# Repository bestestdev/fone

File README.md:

# fone

A modern take on the classic Nokia cell phone experience, built with a Raspberry Pi Pico 2 running MicroPython. This project combines the simplicity and reliability of old-school Nokia phones with quality-of-life improvements for modern usability.

## Overview

**fone** is a DIY cellular phone that captures the essence of classic Nokia devices while incorporating modern components and conveniences. The device features a minimalist design focused on essential communication functions: calls, SMS, and basic navigation, all powered by MicroPython for easy customization and development.

## Hardware Components

### Core Processing
- **Raspberry Pi Pico 2** - Main microcontroller running MicroPython
- **W25Q128 SPI Flash** - 16MB flash storage for contacts, messages, and system data

### Cellular Communication
- **SIM7600G Module** - 4G/LTE cellular connectivity with GPS
- Connected via UART (TX/RX) to Pico 2

### Power Management
- **3700mAh Lithium Battery** - Long-lasting power source
- **TP4056 Charging Module** - Safe battery charging via USB-C
- **MT3608 Boost Converter** - Boost LiPo battery to 5v for use by the SIM module and Pico

### Audio System
- **MAX98357A I2S Amplifier** - Digital audio amplification
- **1W 8Ω Speaker** - Clear audio output for calls and notifications
- **GY-MAX4466 Electret Microphone** - Voice input with AGC
- **ADS1115 ADC** - High-resolution analog-to-digital conversion for microphone

### Display & Input
- **2.42" OLED Display (SSD1309)** - monochrome, 128x64 resolution, SPI interface, low power consumption
- **ANO Directional Navigation and Scroll Wheel Rotary Encoder** - Navigation, selection, scroll, and menu control
- **3V Coin Vibration Motor** - Haptic feedback and notifications

## Features

### Core Functionality
- **Voice Calls** - Make and receive phone calls with clear audio
- **SMS Messaging** - Send and receive text messages
- **Contact Management** - Store and organize phone contacts
- **Call History** - Track incoming, outgoing, and missed calls

### Enhanced User Experience
- **Improved Text Input** - Modern T9-style predictive text with encoder navigation
- **Menu Navigation** - Intuitive interface designed for encoder and directional button control
- **Scroll Wheel Support** - Rotary encoder provides smooth scrolling through lists and menus
- **Low Power Operation** - E-paper display and efficient power management
- **Haptic Feedback** - Vibration for notifications and user interactions

### Additional Features
- **GPS Location (Stretch Goal)** - Built-in positioning via SIM7600G
- **Battery Monitoring** - Real-time battery level and charging status
- **Silent/Vibrate Modes** - Customizable notification preferences
- **Basic Games** - Classic Nokia-style entertainment (Snake, etc.)

## Technical Specifications

### Connectivity
- **Cellular**: 4G LTE via SIM7600G
- **GPS (Stretch Goal)**: Built-in GNSS receiver
- **Storage**: 16MB SPI flash memory (W25Q128)

### Power
- **Battery Life**: All-day usage with 3700mAh capacity
- **Charging**: USB charging via TP4056 module
- **Standby**: Ultra-low power consumption with e-paper display

### Interface
- **Display**: 2.42" monochrome OLED (128x64px)
- **Input**: ANO rotary encoder with directional navigation buttons
- **Audio**: Full-duplex voice communication
- **Feedback**: Vibration motor for alerts

## Software Architecture

- **Platform**: MicroPython on Raspberry Pi Pico 2
- **Modular Design**: Separate modules for cellular, audio, display, and input handling
- **Event-Driven**: Efficient power management through interrupt-based operation
- **Extensible**: Easy to add new features and customize behavior

## Wiring Guide

### SIM7600G to Raspberry Pi Pico 2

The SIM7600G module connects via UART and requires the following connections:

| SIM7600G Pin | Description | Connection | Notes |
|--------------|-------------|------------|-------|
| **V** | VCC | **5V from MT3608** | Requires stable 5V (up to 2A) |
| **G** | Ground | **Battery -** | Battery ground |
| **G** | Ground | **Pico GND** (Pin 38) | Shared ground with Pico |
| **T** | TX (Module transmit) | **GP1** (Pin 2) | UART0 RX |
| **R** | RX (Module receive) | **GP0** (Pin 1) | UART0 TX |
| **K** | Power Key | **GP2** (Pin 4) | GPIO for power control |
| **S** | Status | **GP3** (Pin 5) | GPIO for status monitoring |

#### Key Points:
- **Power**: SIM7600G requires 5V via MT3608 boost converter for proper RF operation
- **Current Draw**: Module can draw up to 2A during transmission bursts
- **UART**: Cross-connect TX/RX (module TX → Pico RX, module RX → Pico TX)
- **Power Key**: Pull HIGH briefly to turn module on/off
- **Status**: Monitor this pin to check if module is powered and ready
- **Dual Ground**: Connect both ground pins for stable operation

### ANO Directional Navigation and Scroll Wheel Rotary Encoder

The primary input is an ANO directional navigation and scroll wheel rotary encoder, providing directional control, rotary scroll input, and a center-press button.

| Encoder Pin | Description | Connection | Notes |
|-------------|-------------|------------|-------|
| **ENCA** | Encoder A Pin | **GP17** (Pin 22) | Rotary encoder quadrature A |
| **ENCB** | Encoder B Pin | **GP22** (Pin 29) | Rotary encoder quadrature B |
| **SW1** | Center Button | **GP6** (Pin 9) | Digital input |
| **SW2** | Down Button | **GP5** (Pin 7) | Digital input |
| **SW3** | Right Button | **GP4** (Pin 6) | Digital input |
| **SW4** | Up Button | **GP19** (Pin 25) | Digital input |
| **SW5** | Left Button | **GP18** (Pin 24) | Digital input |
| **COM** | Common | **GND** (Pin 38) | Common ground for all switches |

#### Key Points:
- **Rotary Encoder**: ENCA/ENCB provide quadrature signals for scroll wheel functionality
- **Digital Buttons**: All switch pins (SW1-SW5) are simple digital inputs
- **Wiring**: Connect the COM pin to GND and configure each GPIO pin as an input with an internal pull-up resistor
- **Active Low**: Button presses and encoder transitions pull pins to ground (LOW)
- **Quadrature Decoding**: Software tracks encoder A/B state changes to determine rotation direction and steps

### Dual Analog Joysticks via ADS1115 ADC

> **Note:** This component has been deprecated and replaced by the ANO Directional Navigation and Scroll Wheel Rotary Encoder.

The phone uses two analog joysticks for navigation and input, connected through an ADS1115 16-bit ADC for full 4-channel analog precision.

**ADS1115 ADC Module:**

| ADS1115 Pin | Description | Connection | Notes |
|-------------|-------------|------------|-------|
| **VDD** | Power | **5V** (Pin 40 - VBUS) | Module power supply |
| **GND** | Ground | **GND** (Pin 38) | Common ground |
| **SCL** | I2C Clock | **GP21** (Pin 27) | I2C0 SCL |
| **SDA** | I2C Data | **GP20** (Pin 26) | I2C0 SDA |
| **ADDR** | Address | **GND** | Sets I2C address to 0x48 |

**Left Joystick (mounted upside down):**

| Joystick Pin | Description | Connection | Notes |
|--------------|-------------|------------|-------|
| **VCC** | Power | **5V** (Pin 40 - VBUS) | Joystick power supply |
| **GND** | Ground | **GND** (Pin 38) | Common ground |
| **VRX** | X-axis analog | **ADS1115 AIN0** | Left joystick X |
| **VRY** | Y-axis analog | **ADS1115 AIN1** | Left joystick Y (inverted) |
| **SW** | Switch button | **GP19** (Pin 25) | Digital input with pull-up |

**Right Joystick:**

| Joystick Pin | Description | Connection | Notes |
|--------------|-------------|------------|-------|
| **VCC** | Power | **5V** (Pin 40 - VBUS) | Joystick power supply |
| **GND** | Ground | **GND** (Pin 38) | Common ground |
| **VRX** | X-axis analog | **ADS1115 AIN2** | Right joystick X |
| **VRY** | Y-axis analog | **ADS1115 AIN3** | Right joystick Y |
| **SW** | Switch button | **GP18** (Pin 24) | Digital input with pull-up |

#### Key Points:
- **Full Analog Control**: ADS1115 provides 4 channels of 16-bit ADC precision
- **I2C Address**: 0x48 (ADDR pin to GND), can be changed for multiple modules
- **Left Joystick**: Mounted upside down, so Y-axis values are inverted in software
- **ADC Resolution**: 16-bit (±32767) with ±4.096V input range matches 5V joysticks
- **Switches**: Active low with internal pull-up resistors on Pico pins (3.3V logic)
- **Update Rate**: ~128 SPS (samples per second) for smooth control

### 3V Vibration Motor

The vibration motor provides haptic feedback for notifications and user interactions.

#### Option 1: Direct GPIO Control (Recommended to try first)

**For Low Current Motors (< 40mA):**

| Motor Pin | Description | Connection | Notes |
|-----------|-------------|------------|-------|
| **+** | Positive | **GP16** (Pin 21) | Direct PWM control |
| **-** | Negative | **GND** (Pin 38) | Direct ground connection |

#### Option 2: Transistor-Protected Control

**For Higher Current Motors (> 40mA) or if direct control fails:**

| Motor Pin | Description | Connection | Notes |
|-----------|-------------|------------|-------|
| **+** | Positive | **GP16** (Pin 21) via NPN Transistor | PWM-controlled output |
| **-** | Negative | **GND** (Pin 38) | Direct ground connection |

**Transistor Circuit (NPN - 2N2222 or similar):**

| Transistor Pin | Description | Connection | Notes |
|----------------|-------------|------------|-------|
| **Base** | Control | **GP16** (Pin 21) via 1kΩ resistor | PWM signal from Pico |
| **Collector** | High side | **Motor +** | Connects to motor positive |
| **Emitter** | Ground | **GND** (Pin 38) | Common ground |

#### Key Points:
- **Motor Specs**: 3V, 12000 RPM, small coin-type vibration motor
- **Current Draw**: Small motors (17-35mA) can connect directly, larger motors (60-105mA) need transistor
- **Pico GPIO Limits**: ~16mA safe, ~50mA maximum per pin
- **Try Direct First**: Start with Option 1 - if motor doesn't work well or Pico gets warm, use Option 2
- **Flyback Diode**: Optional 1N4001 diode across motor (cathode to +, anode to -) for back-EMF protection
- **Control**: PWM control via GP16 allows variable vibration intensity
- **Frequency**: Typical vibration patterns: short bursts (100-300ms) for notifications

### 2.42" OLED Display (SSD1309)

The 2.42" monochrome OLED display provides the main user interface with a 128x64 resolution using SPI communication.

**Display Module Connections:**

| Display Pin | Description | Connection | Notes |
|-------------|-------------|------------|-------|
| **VCC** | Power | **3V3** (Pin 36) | 3.3V power supply |
| **GND** | Ground | **GND** (Pin 38) | Common ground |
| **CLK** | SPI Clock | **GP10** (Pin 14) | SPI1 SCK |
| **DIN** | SPI Data In | **GP11** (Pin 15) | SPI1 MOSI (TX) |
| **CS** | Chip Select | **GP9** (Pin 12) | SPI chip select (active low) |
| **DC** | Data/Command | **GP12** (Pin 16) | Command mode control |
| **RST** | Reset | **GP13** (Pin 17) | Hardware reset (active low) |

#### Key Points:
- **SPI Interface**: Uses SPI1 on Pico 2 for communication
- **Monochrome Display**: Black and white output with high contrast
- **Resolution**: 128x64 pixels provides clear text and simple graphics
- **Fast Updates**: ~10ms refresh time for full screen updates
- **Low Power**: Efficient power consumption (perfect for phone standby)
- **Rotation Support**: Software rotation for portrait or landscape orientation
- **Viewing Angle**: Wide viewing angle (>160°) for clear visibility
- **Compact Size**: 2.42" diagonal with minimal bezel

### W25Q128 SPI Flash Memory Module

The W25Q128 provides 16MB (128Mbit) of non-volatile storage for contacts, messages, and system data, connected via SPI interface. This flash memory offers faster access times and lower power consumption compared to SD cards.

**W25Q128 Module Connections:**

| W25Q128 Pin | Description | Connection | Notes |
|-------------|-------------|------------|-------|
| **VCC** | Power | **3V3** (Pin 36) | 3.3V power supply |
| **GND** | Ground | **GND** (Pin 38) | Common ground |
| **DC** | SPI Data Out (MISO) | **GP8** (Pin 11) | SPI1 MISO (RX) |
| **D1** | SPI Data In (MOSI) | **GP11** (Pin 15) | SPI1 MOSI (TX) - **Shared with display** |
| **SLK** | SPI Clock | **GP10** (Pin 14) | SPI1 SCK - **Shared with display** |
| **CS** | Chip Select | **GP7** (Pin 10) | SPI chip select (active low) |

#### Key Points:
- **Shared SPI Bus**: Uses SPI1 shared with the e-paper display (SLK, D0 pins)
- **Separate MISO**: Flash memory has its own MISO line (D1/GP8) since display is write-only
- **Unique CS**: Each device has its own chip select (Flash: GP7, Display: GP9)
- **Power**: 3.3V operation, low power consumption (4mA active, <1µA standby)
- **Storage**: 16MB of flash memory with 100,000+ erase/program cycles
- **Performance**: Up to 104MHz SPI clock, much faster than SD card access
- **File System**: Can use LittleFS or FAT filesystem via MicroPython's VFS

### MAX98357A I2S Amplifier and Speaker

The MAX98357A is a digital I2S audio amplifier used to drive the speaker for calls, notifications, and other audio feedback.

**MAX98357A Module Connections:**

| MAX98357A Pin | Description | Connection | Notes |
|---------------|-------------|------------|-------|
| **Vin** | Power In | **5V** (Pin 40 - VBUS) | 3-5.5V input range |
| **GND** | Ground | **GND** (Pin 38) | Common ground |
| **DIN** | Data In | **GP20** (Pin 26) | I2S Serial Data |
| **BCLK** | Bit Clock | **GP14** (Pin 19) | I2S Bit Clock |
| **LRC** | Left-Right Clock | **GP15** (Pin 20) | I2S Word Select |
| **SD** | Shutdown | **GP21** (Pin 27) | Active-low shutdown control |
| **GAIN** | Gain Select | *(unconnected)* | Default 9dB gain. Connect to GND for 3dB, VCC for 15dB. |

**Speaker Connection:**

| Component | Connection |
|-----------|------------|
| **Speaker +** | **MAX98357A Left/Right +** |
| **Speaker -** | **MAX98357A Left/Right -** |

#### Key Points:
- **I2S Audio**: Digital audio provides clear, noise-free sound.
- **Power**: Connected to 5V for maximum speaker volume.
- **Shutdown Pin**: GP21 controls the amplifier's shutdown mode to conserve power.
- **Mono Output**: Although the module has L/R outputs, it's a mono amplifier. Connect speaker to either pair.
- **Gain Control**: The `GAIN` pin can be used to adjust the amplification level if needed. Default (unconnected) is 9dB.

### GY-MAX4466 Electret Microphone

The GY-MAX4466 microphone module with automatic gain control (AGC) is used for voice input. It's connected directly to one of the Pico's ADC pins.

**Microphone Module Connections:**

| Microphone Pin | Description | Connection | Notes |
|----------------|-------------|------------|-------|
| **VCC** | Power | **3V3** (Pin 36) | 2.4-5.5V input range |
| **GND** | Ground | **GND** (Pin 38) | Common ground |
| **OUT** | Analog Out | **GP28** (Pin 34) | Connects to ADC2 |

#### Key Points:
- **Direct ADC Connection**: Simplifies wiring and reduces component count.
- **Analog Pin**: Uses `GP28`, one of the Pico's three dedicated ADC pins.
- **Power**: Runs on 3.3V power provided by the Pico.
- **AGC**: The MAX4466's automatic gain control adjusts for varying sound levels.

### Battery Level Monitoring

To monitor the battery level, a voltage divider is used to scale the battery's voltage (3.0V-4.2V) down to a range the Pico's ADC can safely read (0-3.3V). The reading is taken on the now-available ADC pin.

**Voltage Divider Circuit:**

| Component | Connection | Notes |
|-----------|----------------------------------|---------------------------------------|
| **Battery +** | Resistor 1 (R1) - e.g., 100kΩ | Connects to the positive battery terminal |
| **R1 + R2** | **GP26** (Pin 31) & Resistor 2 (R2) | Center point connects to Pico's ADC pin |
| **R2** | **GND** (Pin 38) | Connects to ground |

*A 1:1 ratio (e.g., two 100kΩ resistors) is simple and effective.*

**Pin Connection:**

| Description | Connection | Notes |
|-------------------|------------|----------------------------|
| **Voltage Sense** | **GP26** (Pin 31) | ADC capable pin (ADC0) |

#### Key Points:
- **Voltage Divider**: Essential to prevent damage to the Pico's ADC.
- **Resistor Choice**: Using identical resistors (e.g., 100kΩ) creates a simple 1:2 divider. The actual voltage is `2 * adc_voltage`.
- **ADC Reading**: The software must read the analog value from `GP26` and multiply it by the divider ratio to calculate the true battery voltage.

*[Development in progress - setup instructions coming soon]*

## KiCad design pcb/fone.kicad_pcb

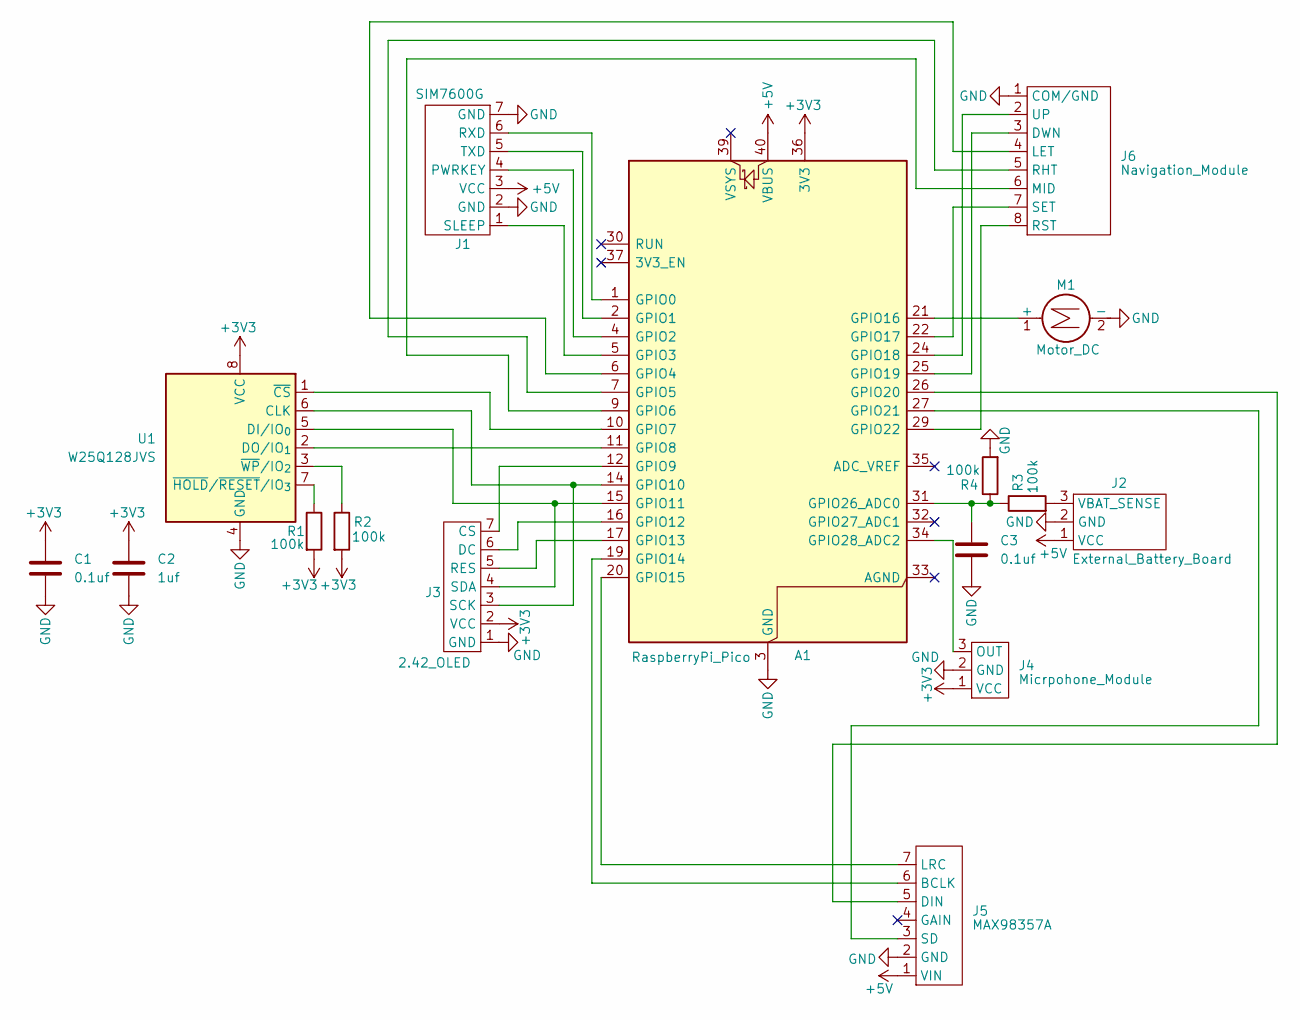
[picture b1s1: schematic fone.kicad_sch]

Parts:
A1: RaspberryPi_Pico; RaspberryPi_Pico_Common_Unspecified
C1, C3: 0.1uf; C_0805_2012Metric_Pad1.18x1.45mm_HandSolder
C2: 1uf; C_0805_2012Metric_Pad1.18x1.45mm_HandSolder
J1: SIM7600G; JST_PH_B7B-PH-K_1x07_P2.00mm_Vertical
J2: External_Battery_Board; JST_PH_B3B-PH-K_1x03_P2.00mm_Vertical
J3: 2.42_OLED; JST_PH_B7B-PH-K_1x07_P2.00mm_Vertical
J4: Micrpohone_Module; JST_PH_B3B-PH-K_1x03_P2.00mm_Vertical
J5: MAX98357A; JST_PH_B7B-PH-K_1x07_P2.00mm_Vertical
J6: Navigation_Module; JST_PH_B8B-PH-K_1x08_P2.00mm_Vertical
M1: Motor_DC; SolderWire-2sqmm_1x02_P7.8mm_D2mm_OD3.9mm
R1, R2, R3, R4: 100k; R_0805_2012Metric_Pad1.20x1.40mm_HandSolder
U1: W25Q128JVS; SOIC-8_5.3x5.3mm_P1.27mm

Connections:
+3V3: A1.36 (3V3), C1.1, C2.1, J3.2 (VCC), J4.1 (VCC), R1.2, R2.2, U1.8 (VCC)
+5V: A1.40 (VBUS), J1.3 (VCC), J2.1 (VCC), J5.1 (VIN)
GND: A1.3 (GND), A1.8 (GND), A1.13 (GND), A1.18 (GND), A1.23 (GND), A1.28 (GND), A1.38 (GND), C1.2, C2.2, C3.2, J1.2 (GND), J1.7 (GND), J2.2 (GND), J3.1 (GND), J4.2 (GND), J5.2 (GND), J6.1 (COM/GND), M1.2 (-), R4.2, U1.4 (GND)
unnamed: A1.1 (GPIO0), J1.6 (RXD)
unnamed: A1.2 (GPIO1), J1.5 (TXD)
unnamed: A1.4 (GPIO2), J1.4 (PWRKEY)
unnamed: A1.5 (GPIO3), J1.1 (SLEEP)
unnamed: A1.6 (GPIO4), J6.4 (LET)
unnamed: A1.7 (GPIO5), J6.5 (RHT)
unnamed: A1.9 (GPIO6), J6.6 (MID)
unnamed: A1.10 (GPIO7), U1.1 (~CS)
unnamed: A1.11 (GPIO8), U1.2 (DO/IO_{1})
unnamed: A1.12 (GPIO9), J3.7 (CS)
unnamed: A1.14 (GPIO10), J3.3 (SCK), U1.6 (CLK)
unnamed: A1.15 (GPIO11), J3.4 (SDA), U1.5 (DI/IO_{0})
unnamed: A1.16 (GPIO12), J3.6 (DC)
unnamed: A1.17 (GPIO13), J3.5 (RES)
unnamed: A1.19 (GPIO14), J5.6 (BCLK)
unnamed: A1.20 (GPIO15), J5.7 (LRC)
unnamed: A1.21 (GPIO16), M1.1 (+)
unnamed: A1.22 (GPIO17), J6.7 (SET)
unnamed: A1.24 (GPIO18), J6.2 (UP)
unnamed: A1.25 (GPIO19), J6.3 (DWN)
unnamed: A1.26 (GPIO20), J5.5 (DIN)
unnamed: A1.27 (GPIO21), J5.3 (SD)
unnamed: A1.29 (GPIO22), J6.8 (RST)
unnamed: A1.31 (GPIO26_ADC0), C3.1, R3.1, R4.1
unnamed: A1.34 (GPIO28_ADC2), J4.3 (OUT)
unnamed: J2.3 (VBAT_SENSE), R3.2
unnamed: R1.1, U1.7 (~HOLD/~RESET/IO_{3})
unnamed: R2.1, U1.3 (~WP/IO_{2})

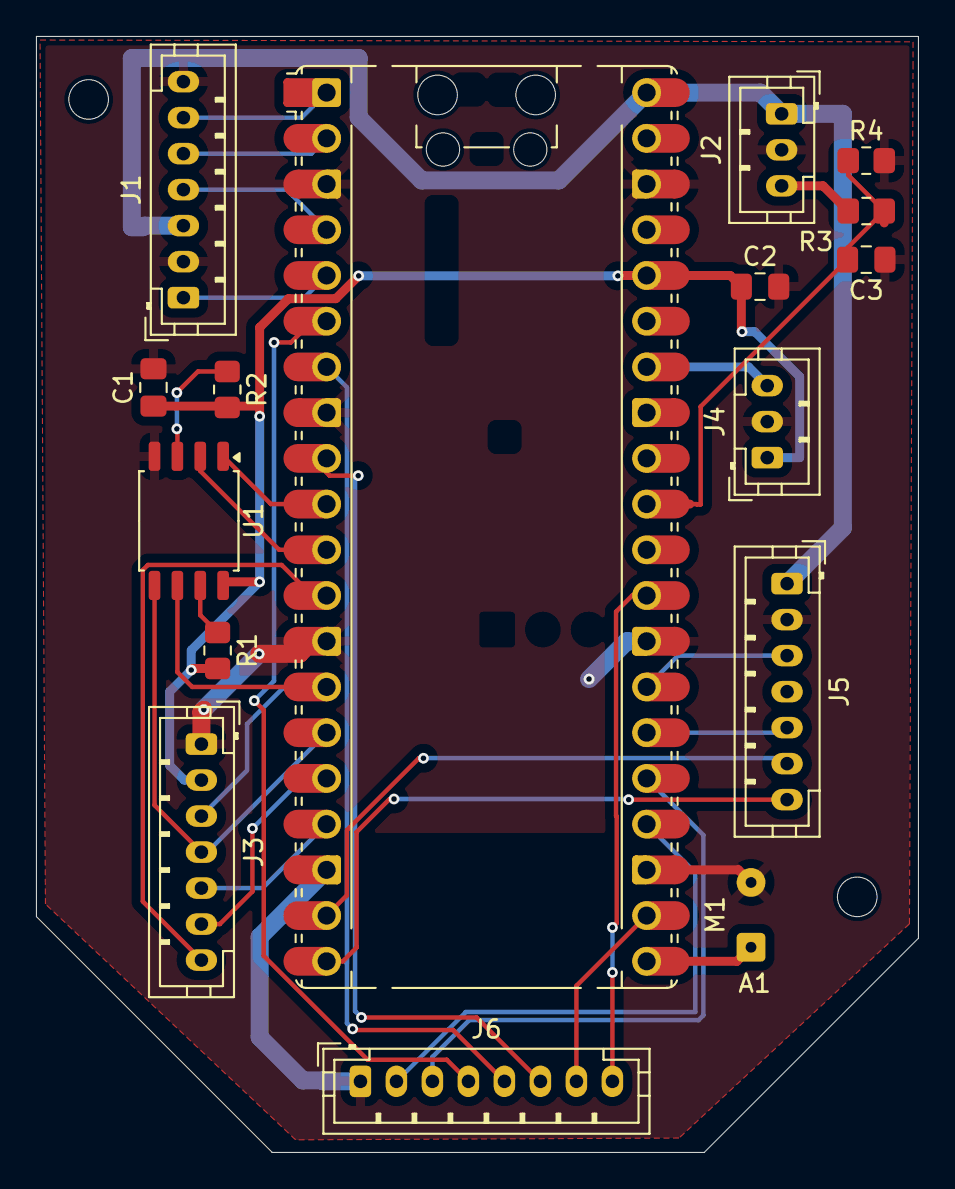
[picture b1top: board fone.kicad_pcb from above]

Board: 2 copper layers, 49.0 x 62.0 mm, 18 parts (0 on the bottom side), 31 nets.

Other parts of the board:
HOLE1, HOLE2: MountingHole_2.2mm_M2

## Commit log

2025-06-04 redmay
2025-06-05 first couple tests with the SIM
2025-06-07 working joysticks
2025-06-07 we gots rumble!
2025-06-07 when combining the display and joysticks for a crosshair test, I realized that oh yeah, e-ink has the garbagest refresh rate and analog isn't the right move. or e ink isn't the right move. will think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
2025-06-10 tried a new display. still not working.
2025-06-12 busted sd card test. probably wrong micropython version or something
2025-06-13 working flash mem! faster, and lower power use. don't need 32GB for this project. 8MB fine.
2025-06-13 working digital navigation module! removing analog joys because they didn't feel right with the low refresh of the e ink
2025-06-13 finally got display working! 3 in a row today
2025-06-17 working speaker and microphone
2025-06-18 moved speaker BCLK to GP15 so we can use GP26 for a battery level indicator. Not sure if that will actually work, but need to wait to test it later
2025-06-18 hardware testing complete! let's make a phone!
2025-06-18 read sms test
2025-06-23 got rotation working on the display, and started working on hw integration tests. and guess what? e paper is slow AF! I knew it was going to be slow, but not 18+ seconds slow. So that's not gonna wor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
2025-07-29 swapped the EPD for an OLED display. I really wanted epaper to work. I think if I didn't expect to include SMS, I could've still gotten away with it. But wow was the display refresh slow.
2025-08-19 added the pcb design
2025-08-31 updated gitignore
2025-08-31 updated kicad and stls
2025-09-01 working with an encoder now!
2025-09-21 phone call test. none of it works
